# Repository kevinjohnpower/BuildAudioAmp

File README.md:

Files required for the design described in the Instructable "Build an Audio Amp From Discrete Components"

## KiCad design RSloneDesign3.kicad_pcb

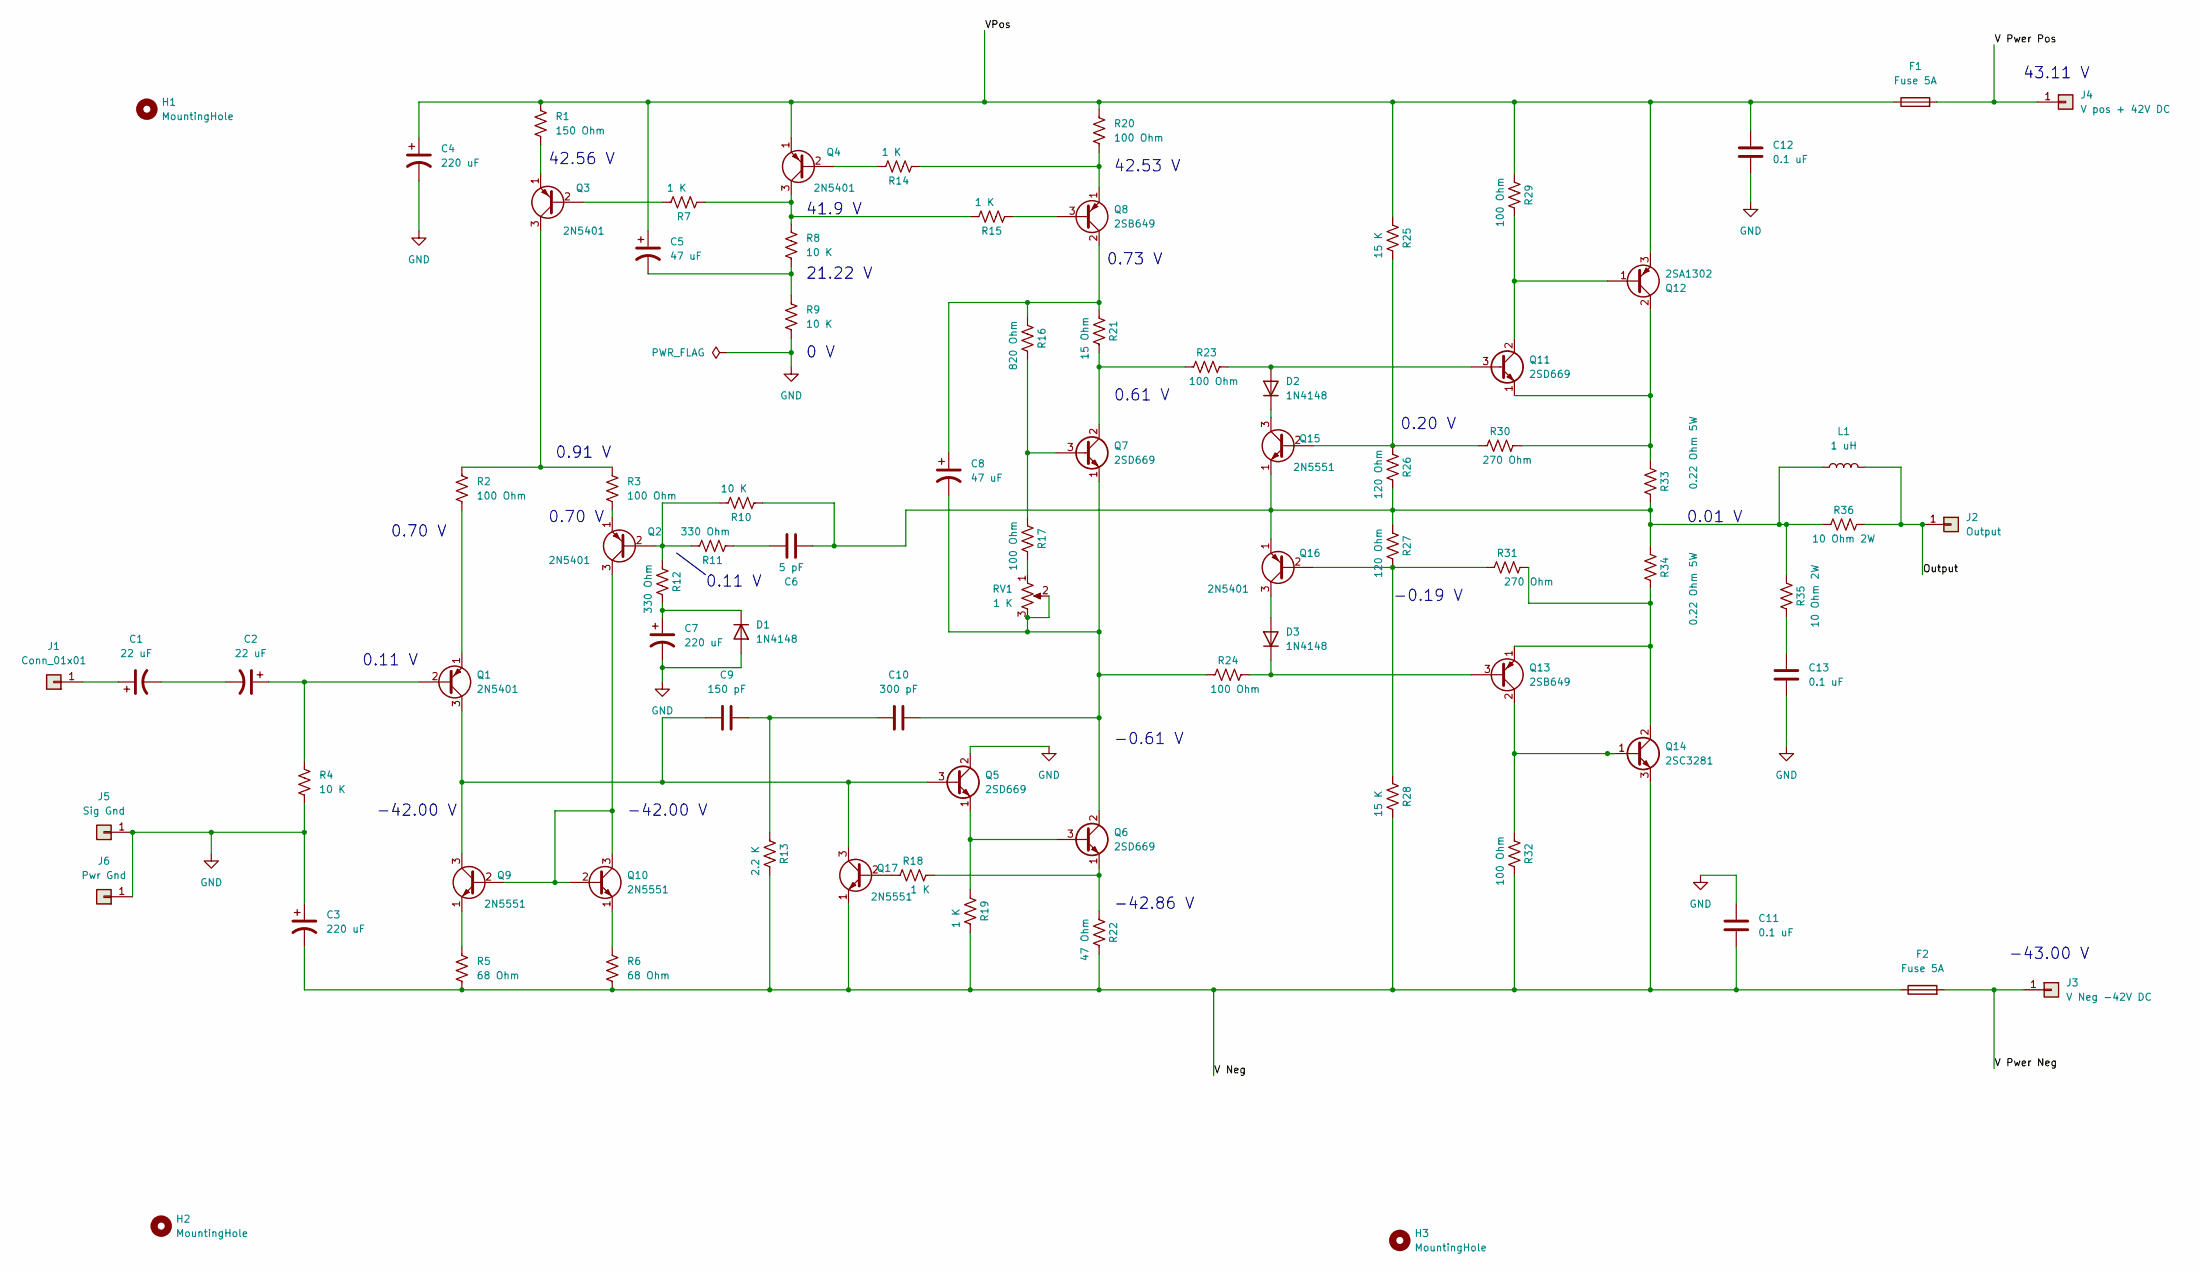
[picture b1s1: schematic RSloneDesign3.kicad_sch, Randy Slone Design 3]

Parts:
C1, C2: 22 uF; CP_Radial_D10.0mm_P7.50mm
C3, C4, C7: 220 uF; CP_Radial_D13.0mm_P7.50mm
C5, C8: 47 uF; CP_Radial_D10.0mm_P7.50mm
C6: 5 pF; C_Axial_L5.1mm_D3.1mm_P10.00mm_Horizontal
C9: 150 pF; C_Axial_L5.1mm_D3.1mm_P10.00mm_Horizontal
C10: 300 pF; C_Axial_L5.1mm_D3.1mm_P10.00mm_Horizontal
C11, C12, C13: 0.1 uF; C_Axial_L5.1mm_D3.1mm_P10.00mm_Horizontal
D1, D2, D3: 1N4148; D_5W_P12.70mm_Horizontal
F1, F2: Fuse 5A; BLX-A Fuse Holder 5mm x 20mm
H1, H2, H3: MountingHole; MountingHole_3.7mm
J1: Conn_01x01; SolderWire-0.75sqmm_1x01_D1.25mm_OD2.3mm
J2: Output; SolderWire-0.25sqmm_1x01_D0.65mm_OD2mm
J3: V Neg -42V DC; SolderWire-0.75sqmm_1x01_D1.25mm_OD2.3mm
J4: V pos + 42V DC; SolderWire-0.75sqmm_1x01_D1.25mm_OD2.3mm
J5: Sig Gnd; SolderWire-0.25sqmm_1x01_D0.65mm_OD2mm
J6: Pwr Gnd; SolderWire-0.75sqmm_1x01_D1.25mm_OD3.5mm
L1: 1 uH; L_Axial_L24.0mm_D7.5mm_P27.94mm_Horizontal_Fastron_MESC
Q1, Q2, Q3, Q4, Q16: 2N5401; TO-92L_Wide
Q5, Q6, Q7, Q11: 2SD669; TO-126-3_Vertical
Q8, Q13: 2SB649; TO-126-3_Vertical
Q9, Q10, Q15, Q17: 2N5551; TO-92L_Wide
Q12: 2SA1302; TO-247-3_Vertical
Q14: 2SC3281; TO-247-3_Vertical
R1: 150 Ohm; R_Axial_DIN0309_L9.0mm_D3.2mm_P15.24mm_Horizontal
R2, R3, R17, R20, R23, R24, R29, R32: 100 Ohm; R_Axial_DIN0309_L9.0mm_D3.2mm_P15.24mm_Horizontal
R4, R8, R9, R10: 10 K; R_Axial_DIN0309_L9.0mm_D3.2mm_P15.24mm_Horizontal
R5, R6: 68 Ohm; R_Axial_DIN0309_L9.0mm_D3.2mm_P15.24mm_Horizontal
R7, R14, R15, R18, R19: 1 K; R_Axial_DIN0309_L9.0mm_D3.2mm_P15.24mm_Horizontal
R11, R12: 330 Ohm; R_Axial_DIN0309_L9.0mm_D3.2mm_P15.24mm_Horizontal
R13: 2.2 K; R_Axial_DIN0309_L9.0mm_D3.2mm_P15.24mm_Horizontal
R16: 820 Ohm; R_Axial_DIN0309_L9.0mm_D3.2mm_P15.24mm_Horizontal
R21: 15 Ohm; R_Axial_DIN0309_L9.0mm_D3.2mm_P15.24mm_Horizontal
R22: 47 Ohm; R_Axial_DIN0309_L9.0mm_D3.2mm_P15.24mm_Horizontal
R25, R28: 15 K; R_Axial_DIN0309_L9.0mm_D3.2mm_P15.24mm_Horizontal
R26, R27: 120 Ohm; R_Axial_DIN0309_L9.0mm_D3.2mm_P15.24mm_Horizontal
R30, R31: 270 Ohm; R_Axial_DIN0309_L9.0mm_D3.2mm_P15.24mm_Horizontal
R33, R34: 0.22 Ohm 5W; R_Axial_Power_L20.0mm_W6.4mm_P25.40mm
R35, R36: 10 Ohm 2W; R_Axial_Power_L20.0mm_W6.4mm_P25.40mm
RV1: 1 K; Potentiometer_Bourns_3296W_Vertical

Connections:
/Output: J2.1, L1.2, R36.1
/V Neg: C3.2, C11.1, F2.1, Q14.3 (E), Q17.1 (E), R5.2, R6.2, R13.1, R19.1, R22.1, R28.1, R32.1
/V Pwer Neg: F2.2, J3.1
/V Pwer Pos: F1.2, J4.1
/VPos: C4.1, C5.1, C12.2, F1.1, Q4.1 (E), Q12.3 (E), R1.2, R20.1, R25.2, R29.2
GND: C3.1, C4.2, C7.2, C11.2, C12.1, C13.1, D1.2 (A), J5.1, J6.1, Q5.2 (C), R4.2, R9.2
unnamed: C1.1, J1.1
unnamed: C1.2, C2.2
unnamed: C2.1, Q1.2 (B), R4.1
unnamed: C5.2, R8.2, R9.1
unnamed: C6.1, R11.2
unnamed: C6.2, L1.1, Q15.1 (E), Q16.1 (E), R10.2, R26.1, R27.2, R33.1, R34.2, R35.2, R36.2
unnamed: C7.1, D1.1 (K), R12.1
unnamed: C8.1, Q8.2 (C), R16.2, R21.2
unnamed: C9.1, Q1.3 (C), Q5.3 (B), Q9.3 (C), Q17.3 (C)
unnamed: C9.2, C10.1, R13.2
unnamed: C8.2, C10.2, Q6.2 (C), Q7.1 (E), R24.2, RV1.2, RV1.3
unnamed: C13.2, R35.1
unnamed: D2.1 (K), Q15.3 (C)
unnamed: D2.2 (A), Q11.3 (B), R23.1
unnamed: D3.1 (K), Q13.3 (B), R24.1
unnamed: D3.2 (A), Q16.3 (C)
unnamed: Q1.1 (E), R2.2
unnamed: Q2.1 (E), R3.2
unnamed: Q2.2 (B), R10.1, R11.1, R12.2
unnamed: Q3.1 (E), R1.1
unnamed: Q3.2 (B), R7.1
unnamed: Q3.3 (C), R2.1, R3.1
unnamed: Q4.2 (B), R14.1
unnamed: Q4.3 (C), R7.2, R8.1, R15.1
unnamed: Q5.1 (E), Q6.3 (B), R19.2
unnamed: Q6.1 (E), R18.1, R22.2
unnamed: Q7.2 (C), R21.1, R23.2
unnamed: Q7.3 (B), R16.1, R17.2
unnamed: Q8.1 (E), R14.2, R20.2
unnamed: Q8.3 (B), R15.2
unnamed: Q9.1 (E), R5.1
unnamed: Q10.1 (E), R6.1
unnamed: Q2.3 (C), Q9.2 (B), Q10.2 (B), Q10.3 (C)
unnamed: Q11.1 (E), Q12.2 (C), R30.1, R33.2
unnamed: Q11.2 (C), Q12.1 (B), R29.1
unnamed: Q13.1 (E), Q14.2 (C), R31.1, R34.1
unnamed: Q13.2 (C), Q14.1 (B), R32.2
unnamed: Q15.2 (B), R25.1, R26.2, R30.2
unnamed: Q16.2 (B), R27.1, R28.2, R31.2
unnamed: Q17.2 (B), R18.2
unnamed: R17.1, RV1.1

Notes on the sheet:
0.70 V
0.91 V
0.61 V
0 V
42.56 V
42.53 V
-42.86 V
41.9 V
-42.00 V
43.11 V
0.01 V
-43.00 V
0.11 V
0.20 V
21.22 V
0.73 V
-0.19 V
-0.61 V

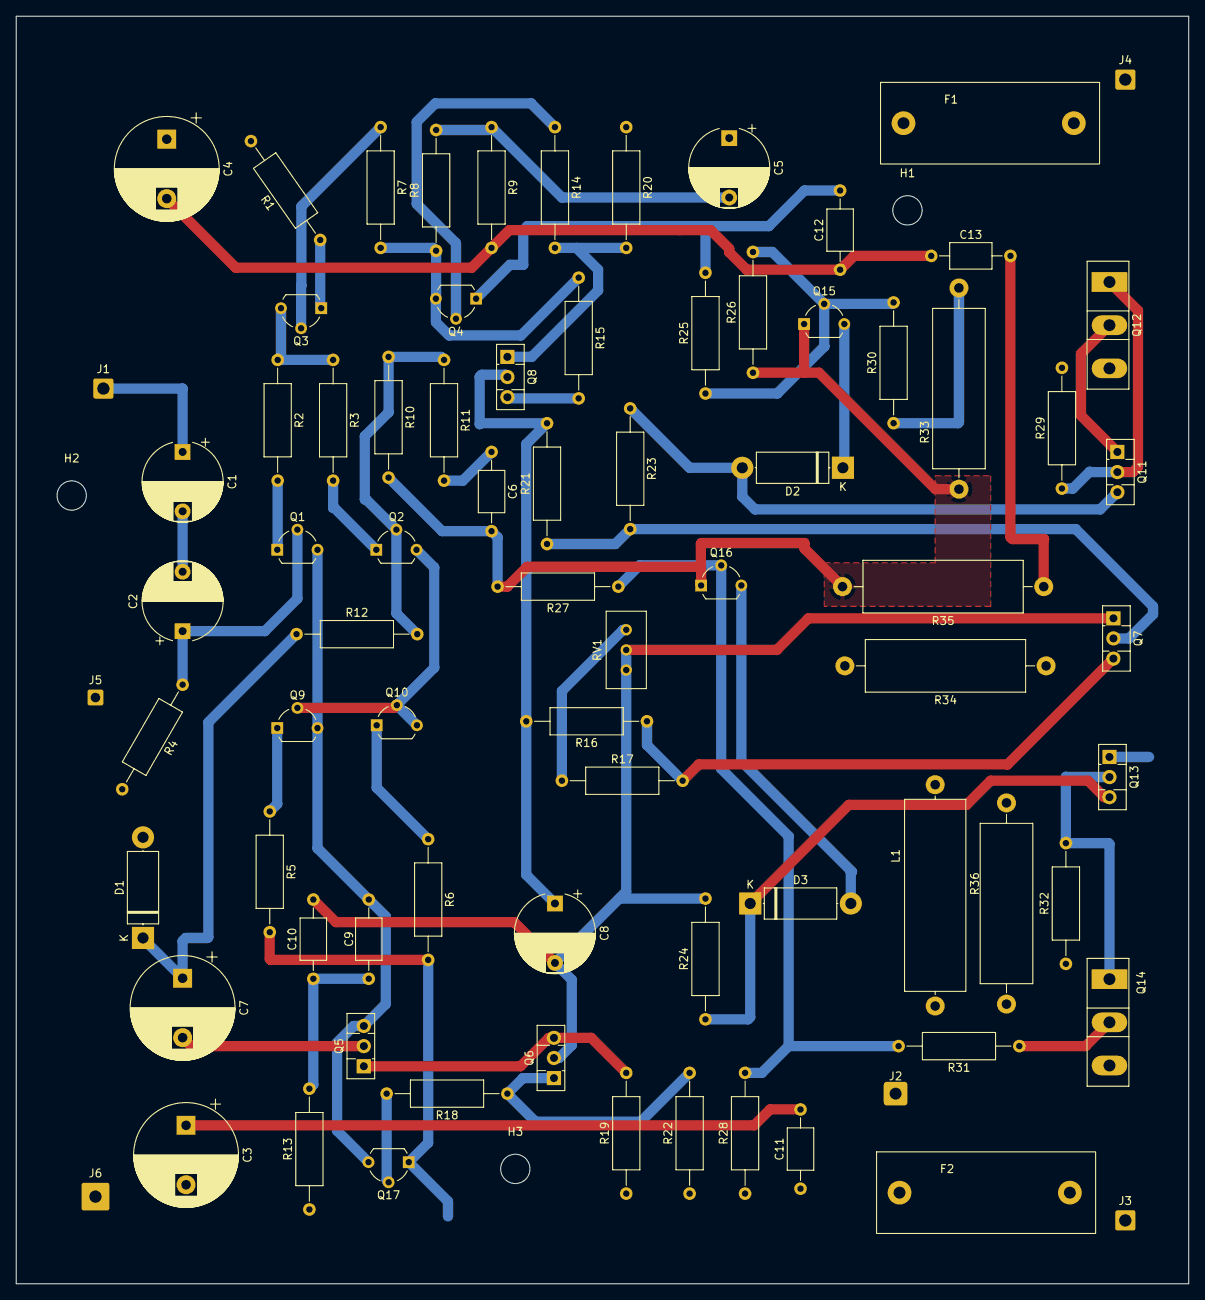
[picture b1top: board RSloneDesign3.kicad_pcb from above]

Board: 2 copper layers, 148.0 x 160.0 mm, 82 parts (0 on the bottom side), 47 nets.

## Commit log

2024-02-05 Gerber files for Design 3
    This zip file contains the Gerber files for the audio amplifier described in the Instructable "Build an Audio Amp from Discrete Components"
2024-02-05 KiCAD files
    KiCAD file for design contained in Instructable "Build an Audio Amp from Discrete Components"
2024-02-05 README.md
